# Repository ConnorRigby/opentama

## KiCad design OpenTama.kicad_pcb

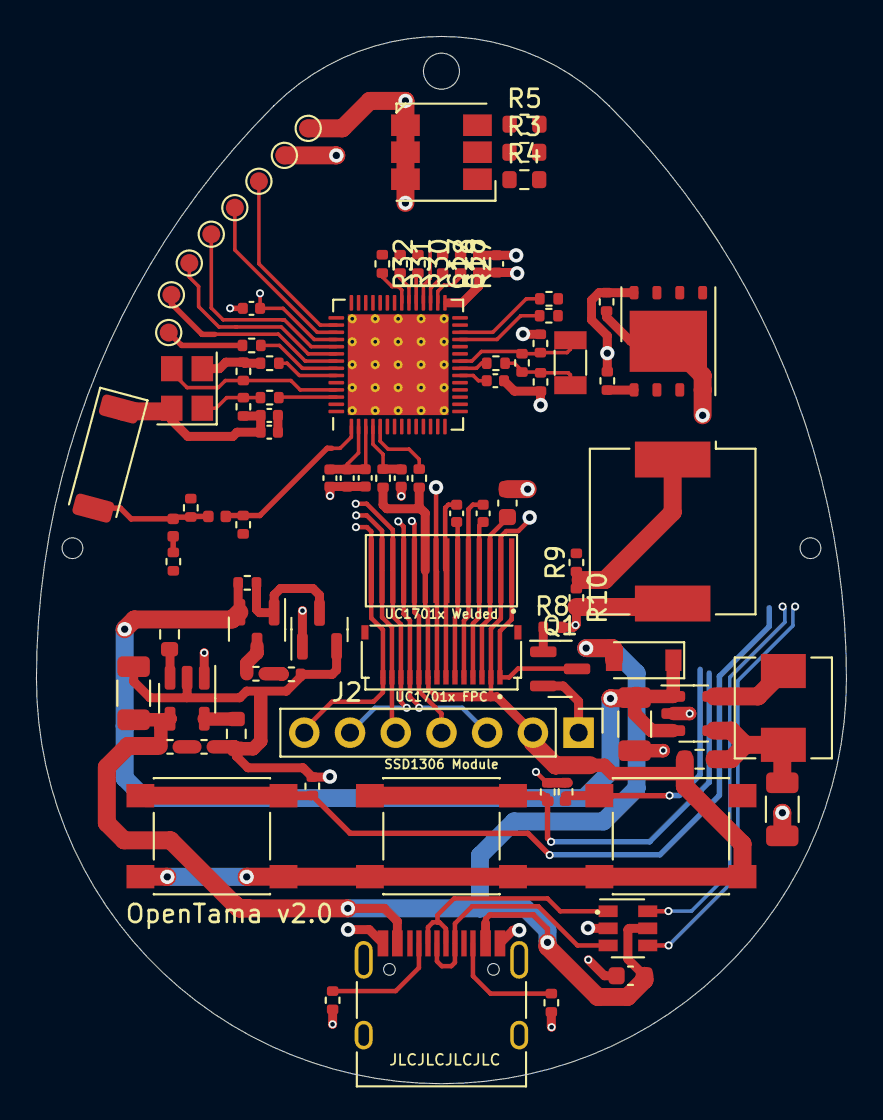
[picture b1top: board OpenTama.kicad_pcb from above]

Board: 4 copper layers, 45.0 x 58.2 mm, 92 parts (1 on the bottom side), 75 nets.

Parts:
AE1: Antenna_Chip; Johanson_2450AT43F0100
BT1: Battery_Cell; Battery_Pads_4x4
C1: 4.7uF; C_1206_3216Metric
C2: 0.1uF; R_0402_1005Metric
C3, C4, C5, C8, C9, C10, C12: C_Small; R_0402_1005Metric
C6: 10uF; C_1206_3216Metric
C7: 1uF; C_1206_3216Metric
C11: 330nF/25V; C_0603_1608Metric
C13, C15: 2.2uF/5V; C_0402_1005Metric
C14, C17, C21, C22: 1uF; C_0402_1005Metric
C16: 100nF; C_0603_1608Metric
C18, C20, C23, C24, C25: 0.1uF; C_0402_1005Metric
C19: 10uF; C_0402_1005Metric
D1: LED_RGB; LED_RGB_TC5050
D2: D_Small; D_SOD-123
J2: Conn_01x14; Hirose_FH34SRJ-14S-0.5SH_1x14-1MP_P0.50mm_Horizontal
J3: Conn_01x07; PinHeader_1x07_P2.54mm_Vertical
J4: USB_C_Receptacle_USB2.0; USB_C_Receptacle_HRO_TYPE-C-31-M-12
J5: Conn_01x14; LCD_14p_0.6mm
L1: 10uH; L_Sunlord_MWSA0518_5.4x5.2mm
L2, L3: L_Small; L_0402_1005Metric
LS1: Speaker_Crystal; Buzzer_CUI_CPT-9019S-SMT
Q1, Q2: BSS138; SOT-23
Q3: BSS84; SOT-23
R1, R2, R8, R13, R14, R25, R35: 10k; R_0402_1005Metric
R3: 1k; R_0603_1608Metric
R4, R5: 330; R_0603_1608Metric
R6: 2k 1%; R_0603_1608Metric
R7, R19: 0; R_0603_1608Metric
R9: 100; R_0402_1005Metric
R10: 1k; R_0402_1005Metric
R11, R20, R21, R23, R24: 20k; R_0402_1005Metric
R12, R15, R27, R28, R30, R31, R32, R33, R34: 0R; R_0402_1005Metric
R16: DNP; R_0402_1005Metric
R17, R18: 5.1k; R_0402_1005Metric
R22: 100k; R_0402_1005Metric
R26: 499; R_0402_1005Metric
SW1: LEFT; SW_Push_1P1T_NO_6x6mm_H9.5mm
SW2: MIDDLE; SW_Push_1P1T_NO_6x6mm_H9.5mm
SW3: RIGHT; SW_Push_1P1T_NO_6x6mm_H9.5mm
TP1: EN; TestPoint_Pad_D1.0mm
TP2: TCK; TestPoint_Pad_D1.0mm
TP3: MTMS; TestPoint_Pad_D1.0mm
TP4: MTDO; TestPoint_Pad_D1.0mm
TP5, TP6: MTDI; TestPoint_Pad_D1.0mm
TP7: RXD; TestPoint_Pad_D1.0mm
TP8: TXD; TestPoint_Pad_D1.0mm
U1: TPS62203DBV; SOT-23-5
U2: LTC4054ES5-4.2; TSOT-23-5
U3: W25Q32JVZP; WSON-8-1EP_6x5mm_P1.27mm_EP3.4x4.3mm
U4: USBLC6-2SC6; SOT-23-6
U5: ESP32-S3R8V; QFN-56-1EP_7x7mm_P0.4mm_EP5.6x5.6mm_ThermalVias
Y1: 40mhz; Crystal_SMD_3225-4Pin_3.2x2.5mm
Y2: 32k; Crystal_SMD_3215-2Pin_3.2x1.5mm

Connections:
+3V3: J2.2, J2.9, J3.2, J5.2, J5.9, R7.1, R11.1, R25.1, SW1.2, SW2.2, SW3.2, TP1.1
+5V: C7.2, C16.1, D2.2 (A), J4.A4 (VBUS), J4.A9 (VBUS), J4.B4 (VBUS), J4.B9 (VBUS), R20.1, U2.4 (VCC), U4.5 (VBUS)
+BATT: BT1.1 (+), C1.1, D2.1 (K), Q3.2 (S), R19.1, R22.1, U1.1 (VI), U1.3 (EN)
-BATT: AE1.1 (FEED), BT1.2 (-), C1.2, C2.1, C3.2, C4.1, C5.1, C6.2, C7.1, C8.2, C9.2, C10.2, C11.2, C12.2, C14.2, C16.2, C17.2, C18.2, C19.2, C20.2, C21.2, C22.2, C23.2, C24.2, C25.2, D1.1 (RK), D1.2 (GK), D1.3 (BK), J2.8, J3.1, J4.A1 (GND), J4.A12 (GND), J4.B1 (GND), J4.B12 (GND), J5.8, LS1.2, Q1.2 (S), Q2.2 (S), R1.2, R2.2, R6.2, R8.2, R10.2, R14.2, R17.1, R18.1, R21.2, R24.2, R35.2, TP6.1, U1.2 (GND), U2.2 (GND), U3.4 (GND), U3.9 (EP), U4.2 (GND), U5.57 (GND), Y1.2, Y1.4
/ESP32-S3/CHIP_PU: C14.1, R25.2, U5.4 (CHIP_PU)
/ESP32-S3/GPIO19: R33.1, U5.25 (GPIO19)
/ESP32-S3/GPIO20: R34.1, U5.26 (GPIO20)
/ESP32-S3/GPIO45: R35.1, U5.51 (GPIO45)
/ESP32-S3/LNA_IN: C12.1, L3.2, U5.1 (LNA_IN)
/ESP32-S3/MCU_MTCK: TP2.1, U5.44 (MTCK)
/ESP32-S3/MCU_MTDI: TP5.1, U5.47 (MTDI)
/ESP32-S3/MCU_MTDO: TP4.1, U5.45 (MTDO)
/ESP32-S3/MCU_MTMS: TP3.1, U5.48 (MTMS)
/ESP32-S3/MCU_SPICLK: R30.2, U5.33 (SPICLK)
/ESP32-S3/MCU_SPICS0: R13.2, U3.1 (~CS), U5.32 (SPICS0)
/ESP32-S3/MCU_SPID: R32.2, U5.35 (SPID)
/ESP32-S3/MCU_SPIHD: R27.2, U5.30 (SPIHD)
/ESP32-S3/MCU_SPIQ: R31.2, U5.34 (SPIQ)
/ESP32-S3/MCU_SPIWP: R28.2, U5.31 (SPIWP)
/ESP32-S3/MCU_U0RXD: R26.2, U5.50 (U0RXD)
/ESP32-S3/MCU_XTAL32_N: C10.1, R16.2, U5.22 (XTAL_32K_N), Y2.2
/ESP32-S3/MCU_XTAL32_P: R15.1, U5.21 (XTAL_32K_P)
/ESP32-S3/MCU_XTAL_N: C9.1, U5.53 (XTAL_N), Y1.3
/ESP32-S3/MCU_XTAL_P: R12.1, U5.54 (XTAL_P)
/ESP32-S3/RF_ANT: AE1.2 (PCB_Trace), C8.1, L2.2, L3.1
/ESP32-S3/SPICLK: R30.1, U3.6 (CLK)
/ESP32-S3/SPID: R32.1, U3.5 (DI(IO0))
/ESP32-S3/SPIHD: R27.1, U3.7 (IO3)
/ESP32-S3/SPIQ: R31.1, U3.2 (DO(IO1))
/ESP32-S3/SPIWP: R28.1, U3.3 (IO2)
/ESP32-S3/U0RXD: R26.1, TP7.1
/ESP32-S3/U0TXD: TP8.1, U5.49 (U0TXD)
/ESP32-S3/VCC_SPI: C2.2, R13.1, U3.8 (VCC)
/ESP32-S3/VDDA: C21.1, C23.1, U5.55 (VDDA1), U5.56 (VDDA2)
/ESP32-S3/VDD_3P3: C19.1, C22.1, C24.1, U5.2 (VDD3P3), U5.3 (VDD3P3)
/ESP32-S3/VDD_CPU: C20.1, U5.46 (VDD3P3_CPU)
/ESP32-S3/VDD_RTC: C25.1, U5.20 (VDD3P3_RTC)
/ESP32-S3/VDD_SPI: C17.1, C18.1, U5.29 (VDD_SPI)
/ESP32-S3/XTAL32_P: C5.2, R15.2, R16.1, Y2.1
/ESP32-S3/XTAL_P: C4.2, R12.2, Y1.1
/GPIO0: R11.2, U5.5 (GPIO0)
BL_EN: Q1.1 (G), R8.1
LEFT_BTN: R14.1, SW1.1
MIDDLE_BTN: R1.1, SW2.1
unnamed: C3.1, L2.1
unnamed: C6.1, L1.2, R7.2, U1.4 (FB)
unnamed: C11.1, J2.3, J5.3
unnamed: C13.1, J2.6, J5.6
unnamed: C13.2, J2.7, J5.7
unnamed: C15.1, J2.4, J5.4
unnamed: C15.2, J2.5, J5.5
unnamed: D1.4 (BA), R5.2
unnamed: D1.5 (GA), R4.2
unnamed: D1.6 (RA), R3.2
unnamed: J2.1, J5.1, Q1.3 (D)
unnamed: J4.A5 (CC1), R17.2
unnamed: J4.B5 (CC2), R18.2
unnamed: L1.1, U1.5 (SW)
unnamed: LS1.1, R9.1, R10.1
unnamed: Q2.3 (D), Q3.1 (G), R22.2
unnamed: Q3.3 (D), R23.1
unnamed: R6.1, U2.5 (PROG)
unnamed: R19.2, U2.3 (BAT)
RIGHT_BTN: R2.1, SW3.1
SCREEN_CLK: J2.11, J3.3, J5.11
SCREEN_CS: J2.14, J3.7, J5.14
SCREEN_DC: J2.12, J3.6, J5.12
SCREEN_DIN: J2.10, J3.4, J5.10
SCREEN_RES: J2.13, J3.5, J5.13
USB_CONN_D+: J4.A6 (D+), J4.B6 (D+), U4.3 (I/O2)
USB_CONN_D-: J4.A7 (D-), J4.B7 (D-), U4.1 (I/O1)
USB_D+: R34.2, U4.4 (I/O2)
USB_D-: R33.2, U4.6 (I/O1)
VBATT_ANA: R23.2, R24.1
VBUS_SENSE: R20.2, R21.1

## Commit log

2022-05-11 Redesign with ESP32

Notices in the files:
OpenTama.kicad_pcb:
Licensed under CERN-OHL-S v2
